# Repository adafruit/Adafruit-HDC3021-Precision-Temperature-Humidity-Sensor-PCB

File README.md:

## Adafruit HDC3021 Precision Temperature Humidity Sensor - STEMMA QT / Qwiic PCB

<a href="http://www.adafruit.com/products/5989"><br/>
Click here to purchase one from the Adafruit shop</a>

PCB files for the Adafruit HDC3021 Precision Temperature Humidity Sensor - STEMMA QT / Qwiic. 

Format is EagleCAD schematic and board layout
* https://www.adafruit.com/product/5989

### Description

We stock a large number of Temperature/Humidity sensors, so you're probably wondering why another one? Well, this Adafruit HDC3021 Precision Temperature & Humidity Sensor breakout features the highest accuracy & precision one we've see so far! It has the TI HDC302x series chip with typical 0.5% accuracy for the RH sensor (with 0.19% long-term drift) and ±0.1°C typical accuracy for the temperature sensor. All at a very nice price.

This sensor has a true I2C interface for easy interfacing with only two wires (plus power and ground!). That makes it preferable to the janky DHT11/DHT22 sensors. The sensor is 5V safe, so you can use 1.8V to 5V power and logic levels without the need for shifters, so you can power and communicate with it using any microcontroller or microcomputer. With 4 selectable I2C addresses, you can have multiple sensors on one bus - unlike many other fixed-address T/RH sensors.

We've written a full-featured Arduino and CircuitPython/Python library, so whether you have an 8-bit microcontroller or a quad-core Raspberry Pi, you will be able to quickly get data from the sensor for your environmental monitoring needs. The library can setup the sensor rate/power, heater, alerts, offsets, and read data or NIST tracking ID.

Such a lovely chip - so we spun up a breakout board with the HDC3021 and some supporting circuitry such as pullup resistors and capacitors. To make things even easier, we've included SparkFun Qwiic compatible STEMMA QT connectors for the I2C bus so you don't even need to solder! QT Cable is not included, but we have a variety in the shop. 

If you prefer working on a breadboard, each order comes with one fully assembled and tested PCB breakout and a small piece of header. You'll need to solder the header onto the PCB, but it's fairly easy and takes only a few minutes even for a beginner. 

Please note: this sensor comes with a protective polyamide sticker on top, please remove before usage!

### License

Adafruit invests time and resources providing this open source design, please support Adafruit and open-source hardware by purchasing products from [Adafruit](https://www.adafruit.com)!

Designed by Limor Fried/Ladyada for Adafruit Industries.

Creative Commons Attribution/Share-Alike, all text above must be included in any redistribution. 
See license.txt for additional details.

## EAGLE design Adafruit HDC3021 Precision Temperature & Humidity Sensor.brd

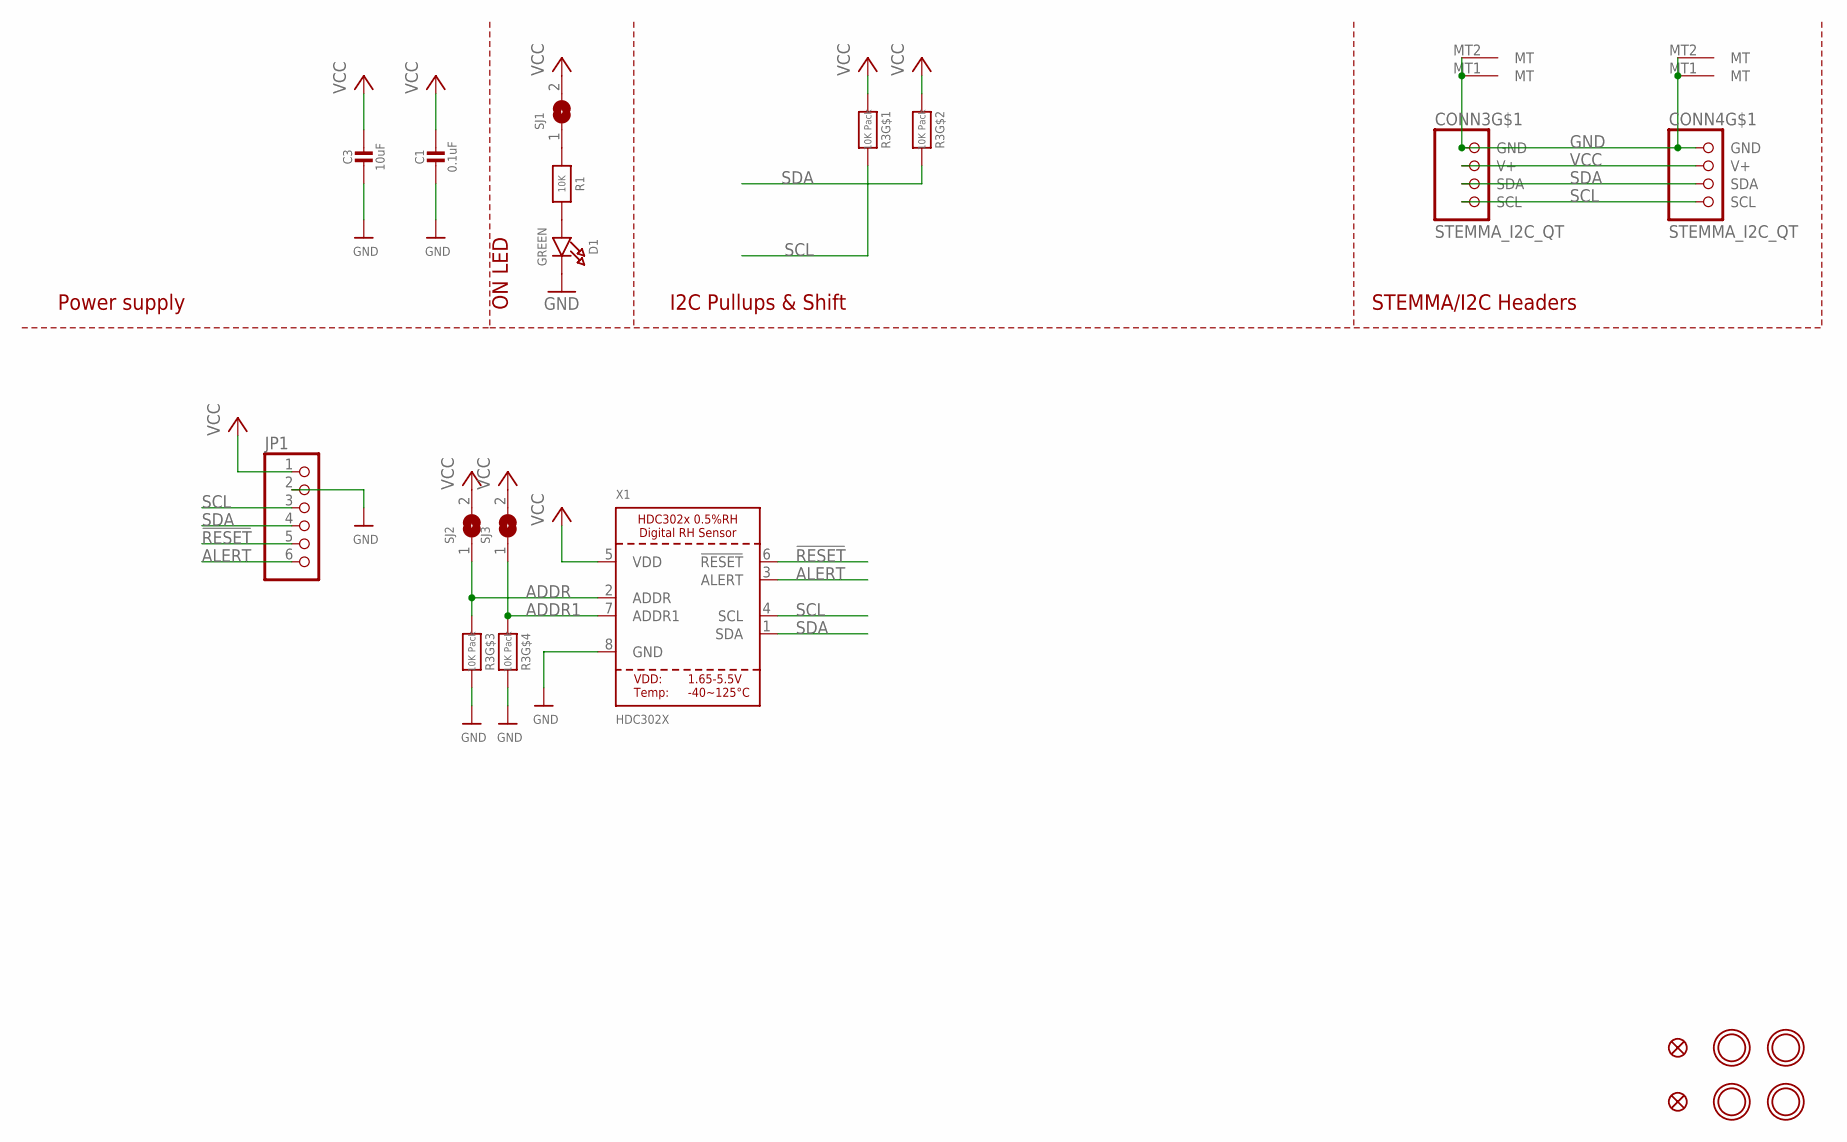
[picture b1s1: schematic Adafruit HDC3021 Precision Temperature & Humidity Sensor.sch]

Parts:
C1: 0.1uF; 0603-NO
C3: 10uF; 0805-NO
CONN3, CONN4: STEMMA_I2C_QT; JST_SH4
D1: GREEN; CHIPLED_0603_NOOUTLINE
FID3, FID4: FIDUCIAL_1MM
JP1: HEADER-1X670MIL; 1X06_ROUND_70
R1: 10K; 0603-NO
R3: 10K Pack; RESPACK_4X0603
SJ1: SOLDERJUMPERCLOSED; SOLDERJUMPER_CLOSEDWIRE
SJ2, SJ3: SOLDERJUMPER; SOLDERJUMPER_ARROW_NOPASTE
U$1, U$17, U$19, U$21: MOUNTINGHOLE2.5; MOUNTINGHOLE_2.5_PLATED
X1: HDC302X; WSON8

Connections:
!RESET: JP1.5, X1.6 (!RESET)
ADDR: R3.3 (1), SJ2.1, X1.2 (ADDR)
ADDR1: R3.4 (1), SJ3.1, X1.7 (ADDR1)
ALERT: JP1.6, X1.3 (ALERT)
GND: C1.2, C3.2, CONN3.1 (GND), CONN3.MT1 (MT), CONN3.MT2 (MT), CONN4.1 (GND), CONN4.MT1 (MT), CONN4.MT2 (MT), D1.C, JP1.2, R3.5 (2), R3.6 (2), X1.8 (GND)
unnamed: D1.A, R1.2
unnamed: R1.1, SJ1.1
SCL: CONN3.4 (SCL), CONN4.4 (SCL), JP1.3, R3.8 (2), X1.4 (SCL)
SDA: CONN3.3 (SDA), CONN4.3 (SDA), JP1.4, R3.7 (2), X1.1 (SDA)
VCC: C1.1, C3.1, CONN3.2 (V+), CONN4.2 (V+), JP1.1, R3.1, R3.2 (1), SJ1.2, SJ2.2, SJ3.2, X1.5 (VDD)

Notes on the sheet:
I2C Pullups & Shift
STEMMA/I2C Headers
ON LED
Power supply

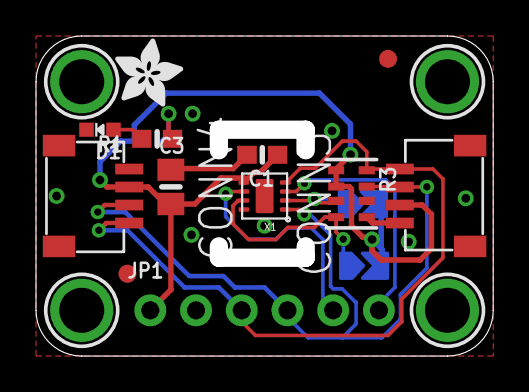
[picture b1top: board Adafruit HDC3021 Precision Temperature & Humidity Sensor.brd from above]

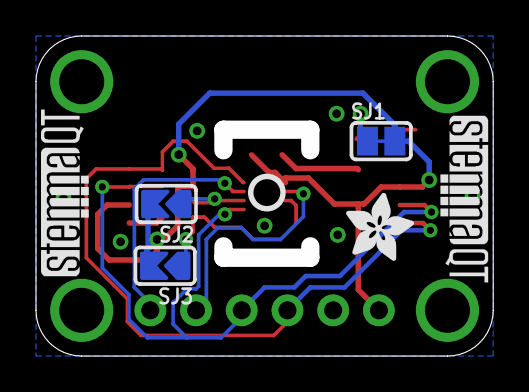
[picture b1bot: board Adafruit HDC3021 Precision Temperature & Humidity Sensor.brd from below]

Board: 2 copper layers, 24.4 x 16.8 mm, 39 parts (14 on the bottom side), 10 nets.

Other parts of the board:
PLABEL0: PLABEL0
PLABEL1: PLABEL1
PLABEL2: PLABEL2
PLABEL3: PLABEL3
PLABEL4: PLABEL4
PLABEL5: PLABEL5
PLABEL6: PLABEL6
PLABEL7: PLABEL7
PLABEL8: PLABEL8
PLABEL9: PLABEL9
PLABEL10: PLABEL10
PLABEL11: PLABEL11
PLABEL12: PLABEL12
PLABEL13: PLABEL13
PLABEL14: PLABEL14
PLABEL15: PLABEL15
U$7, U$22: ADAFRUIT_3.5MM
U$25: PCBFEAT-REV-040
U$30, U$31: STEMMAQT

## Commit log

2024-07-08 cookiecutter
2024-07-08 rename

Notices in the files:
parts and their libraries:
microbuilder: This work is placed in the public domain, and may be freely used for commercial and non-commercial work with the following conditions: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
